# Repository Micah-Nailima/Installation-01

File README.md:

# Installation-01
A 75% keyboard with magnetic rotary encoders and a build in USB hub for additional peripherals such as a numpad and midi controller.

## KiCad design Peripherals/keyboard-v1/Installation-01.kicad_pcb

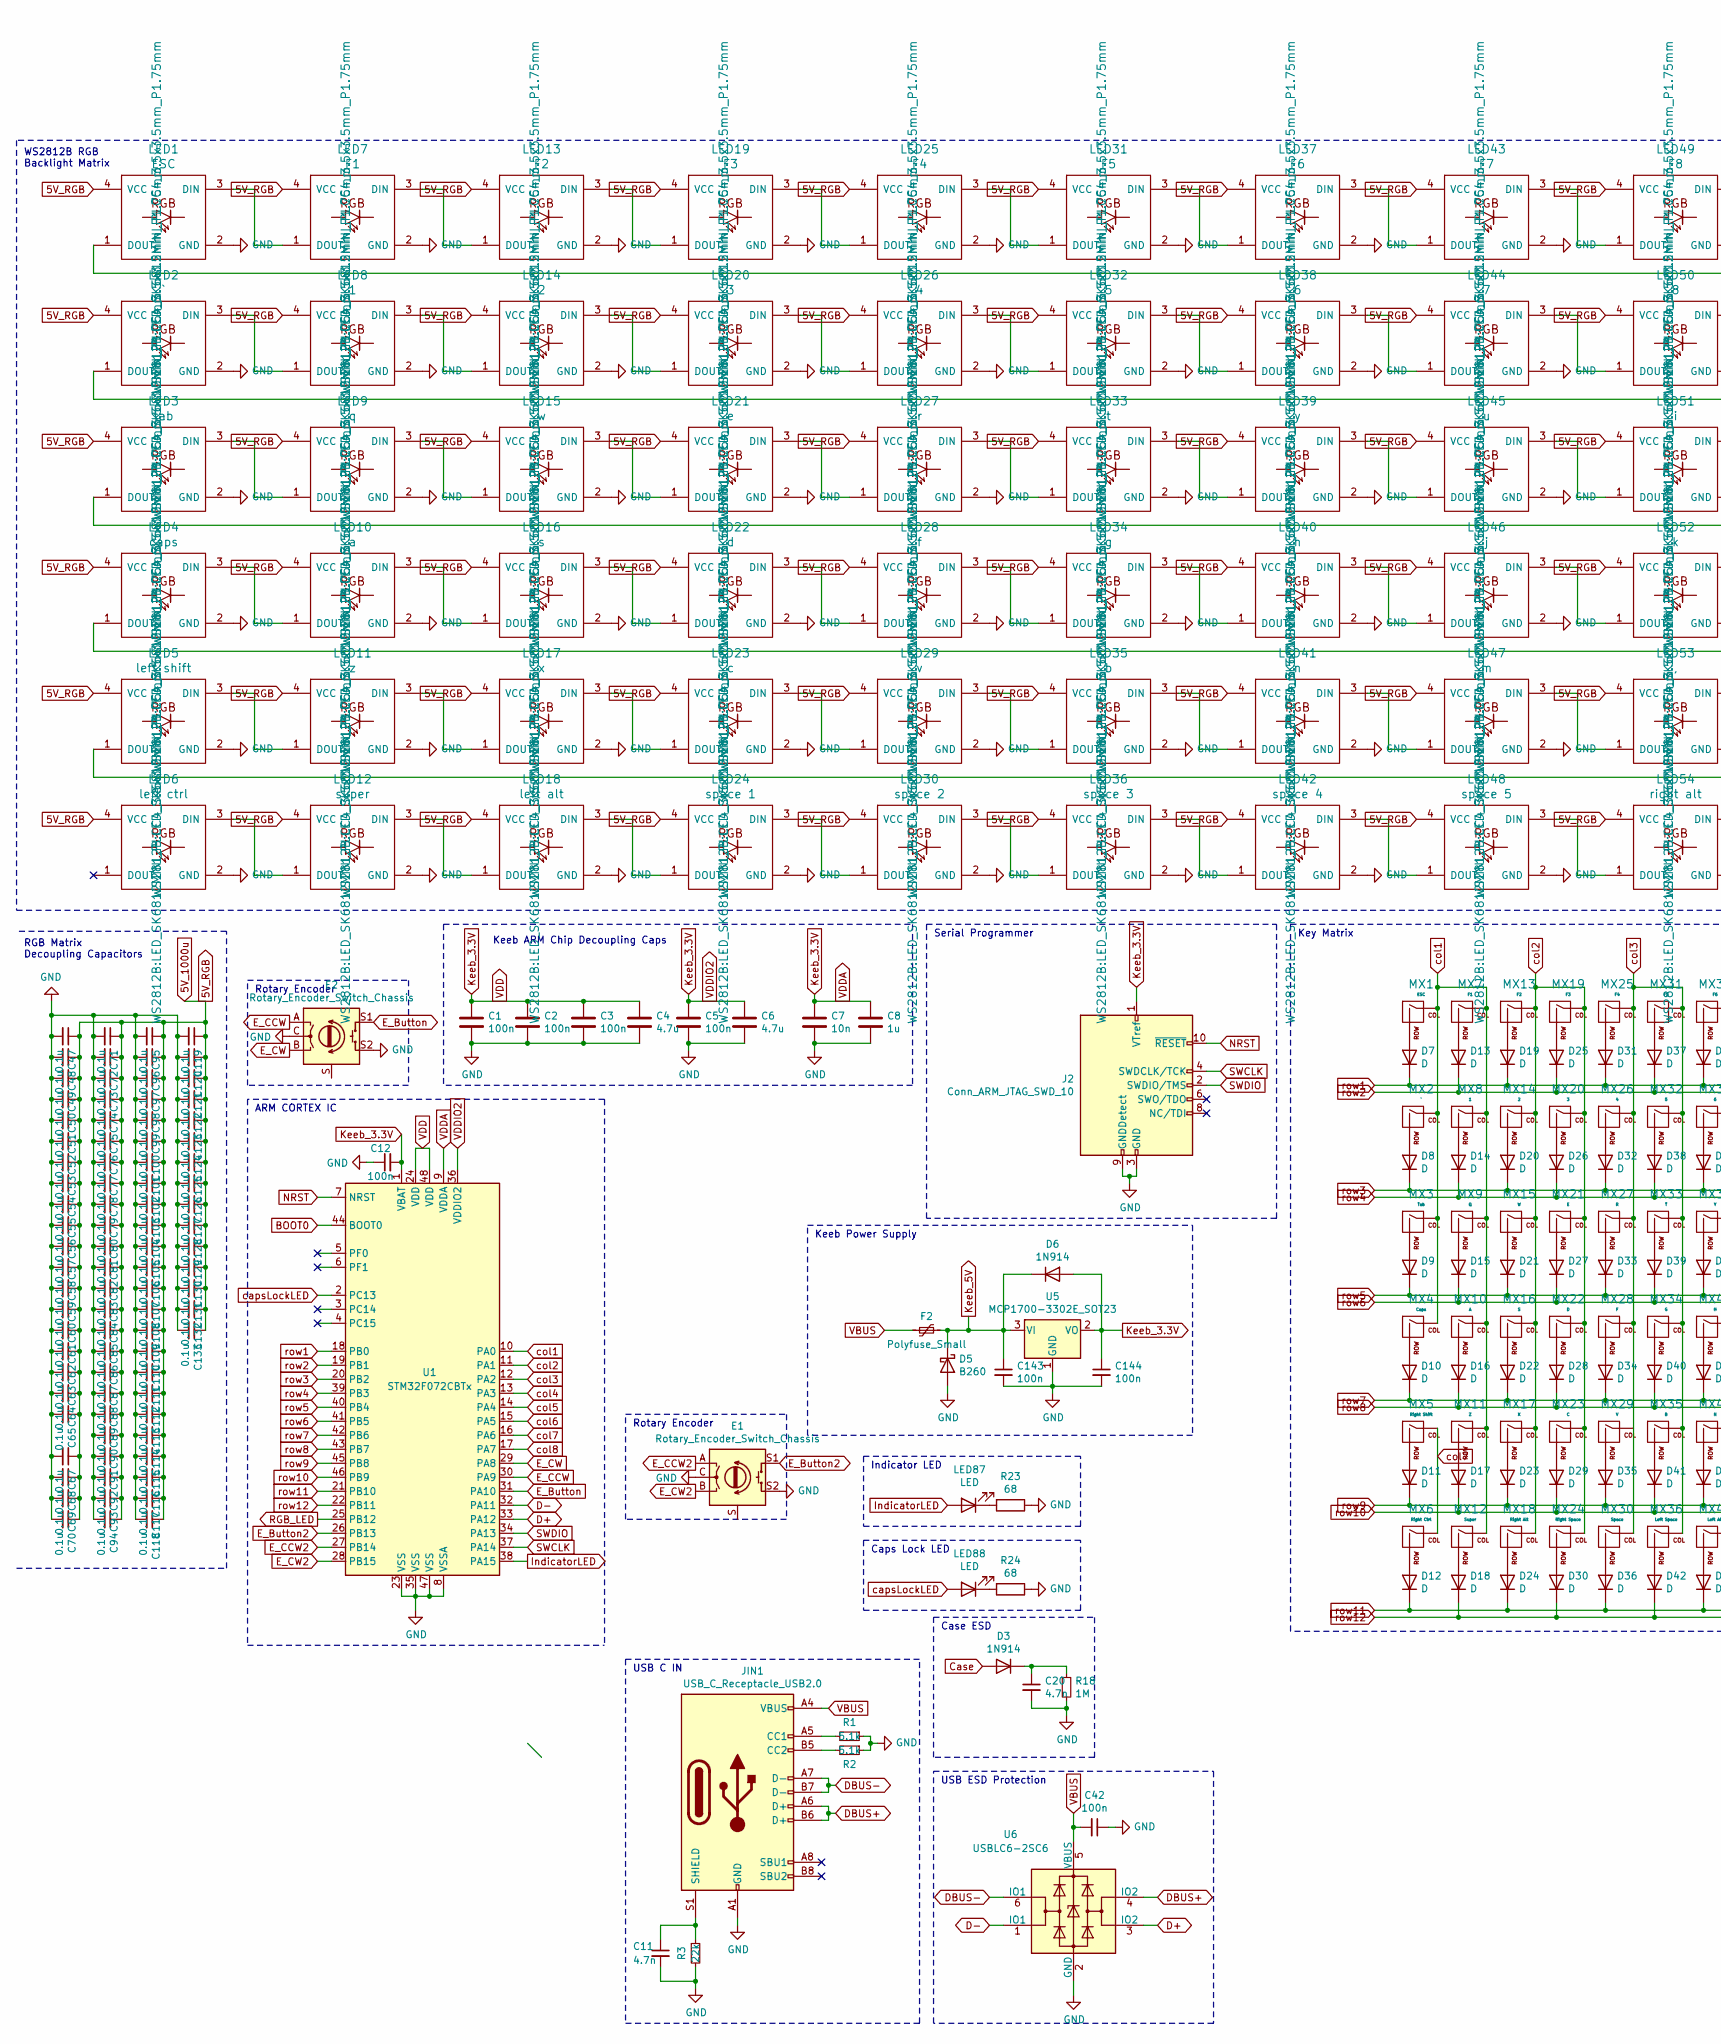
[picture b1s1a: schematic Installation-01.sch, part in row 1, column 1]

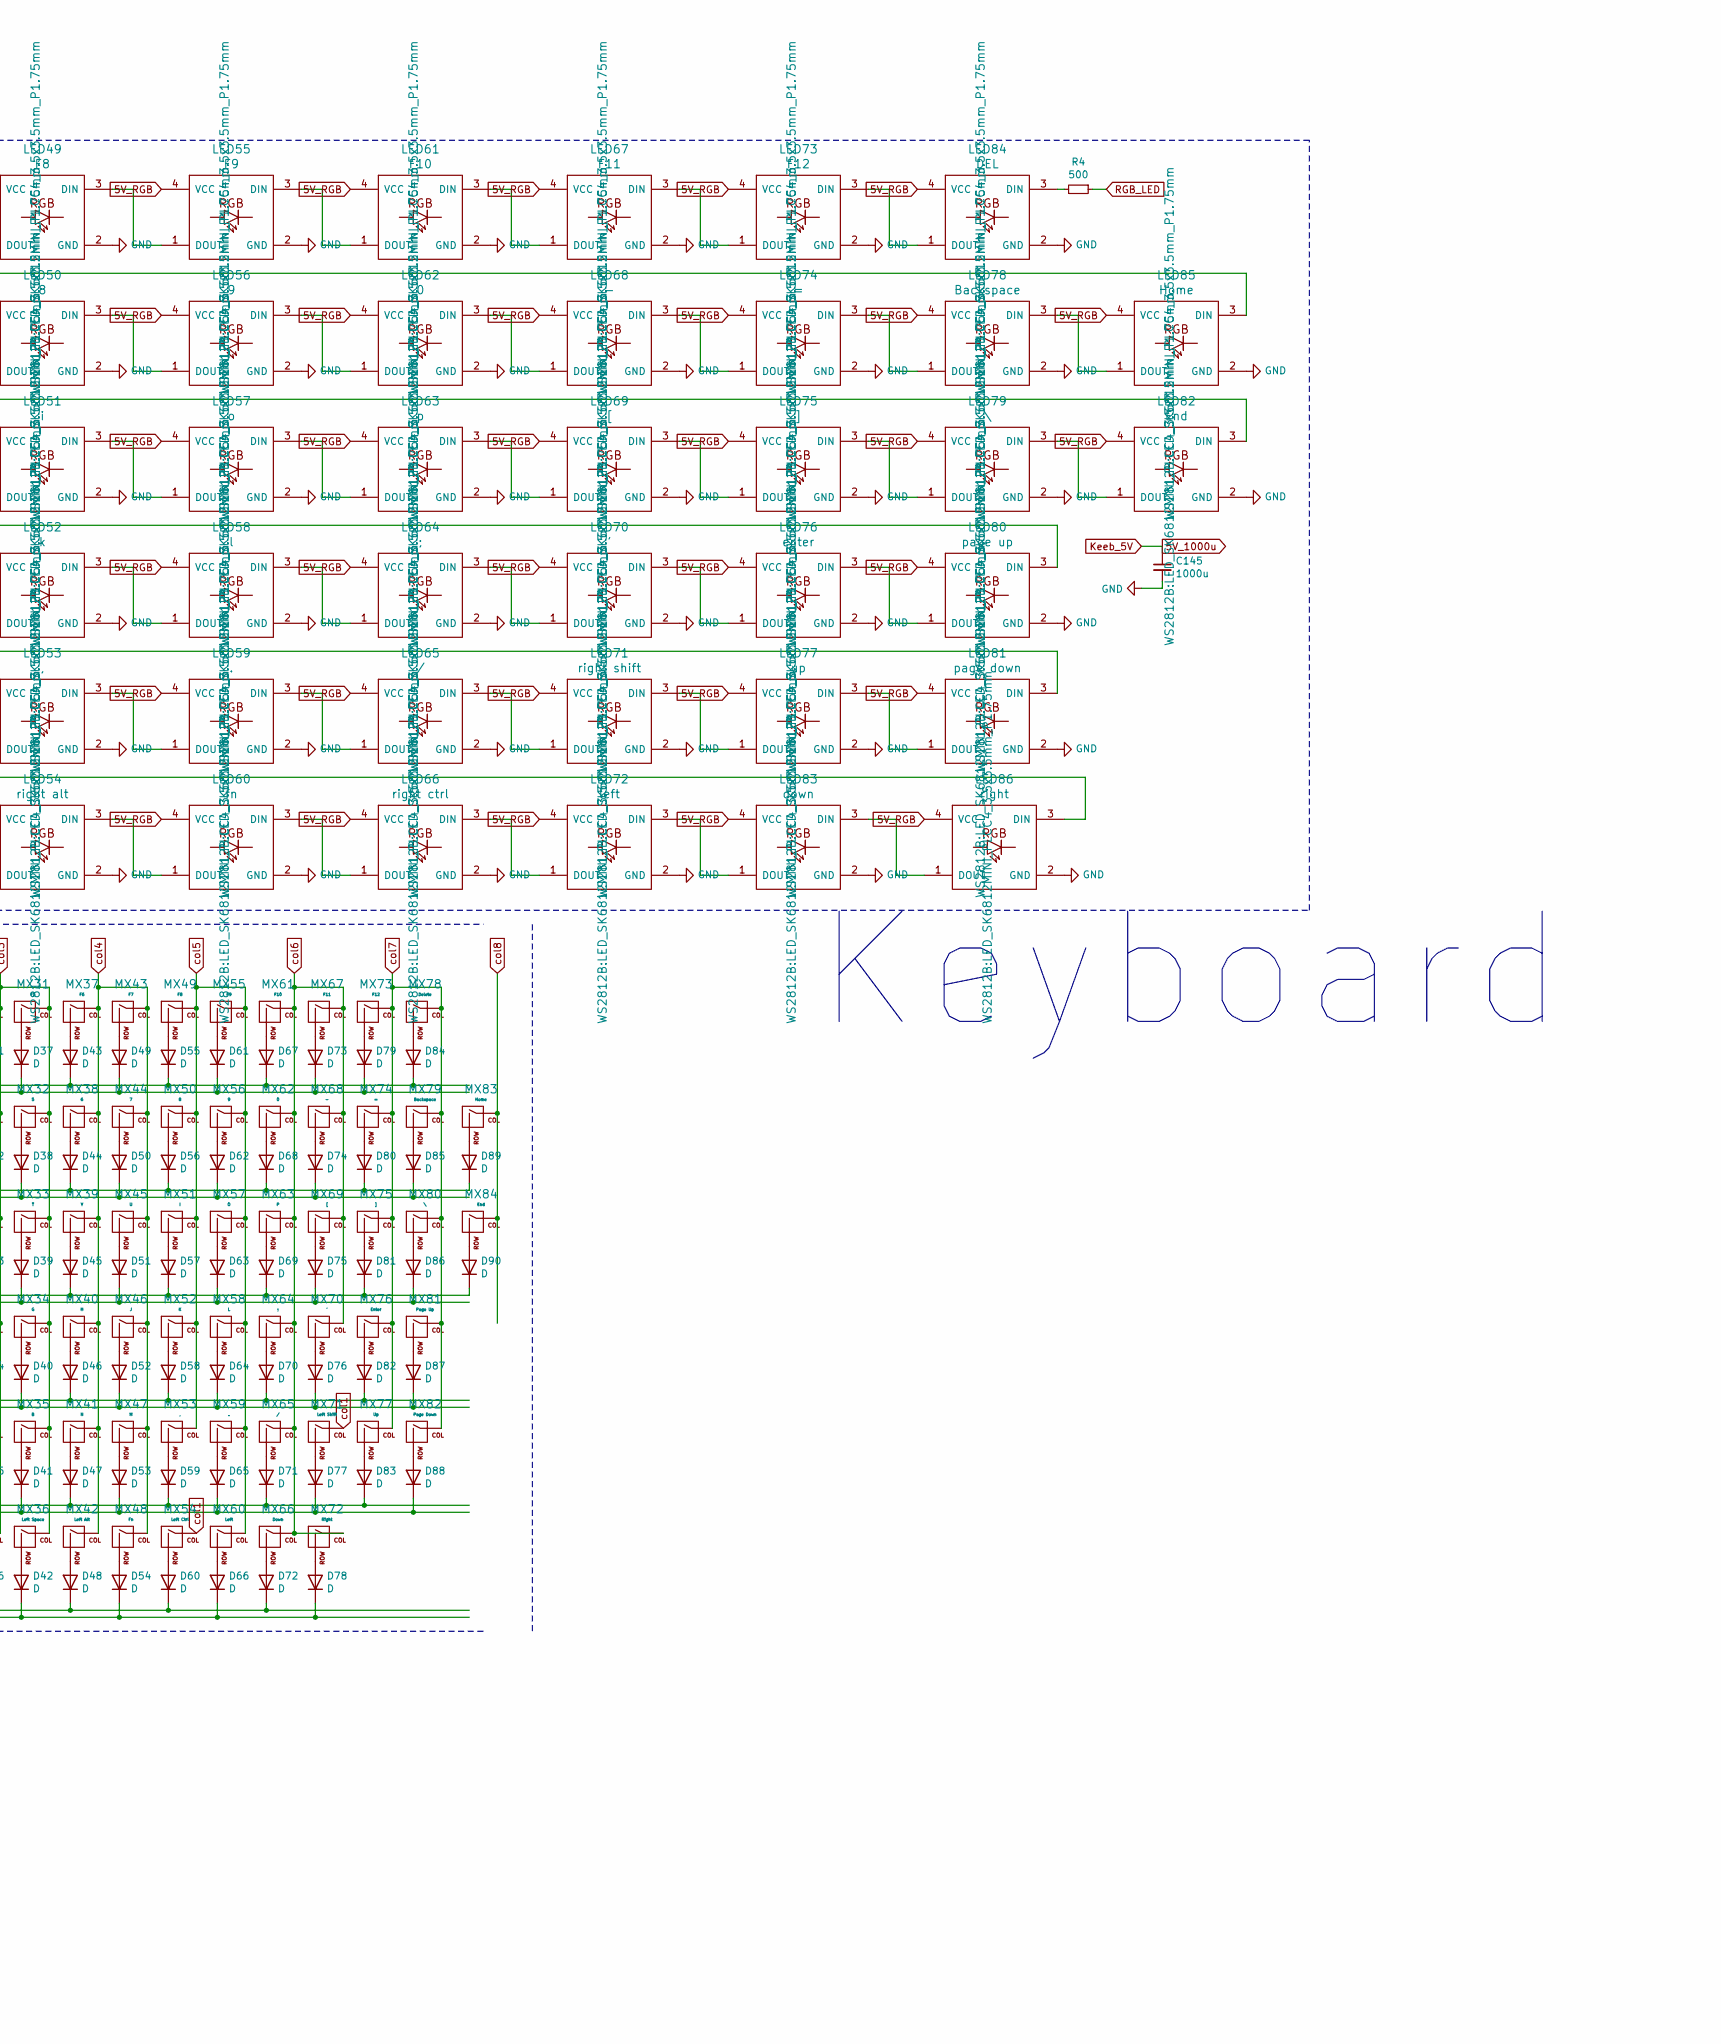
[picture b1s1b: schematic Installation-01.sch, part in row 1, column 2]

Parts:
C1, C2, C3, C5, C12, C42, C143, C144: 100n; CP_EIA-2012-15_AVX-P
C4, C6: 4.7u; CP_EIA-2012-15_AVX-P
C7: 10n; CP_EIA-2012-15_AVX-P
C8: 1u; CP_EIA-2012-15_AVX-P
C11, C20: 4.7n; CP_EIA-2012-15_AVX-P
C47, C48, C49, C50, C51, C52, C53, C54, C55, C56, C57, C58, C59, C60, C61, C62, C63, C64, C65, C67, C68, C69, C70, C71, C72, C73, C74, C75, C76, C77, C78, C79, C80, C81, C82, C83, C84, C85, C86, C87, C88, C89, C90, C91, C92, C93, C94, C95, C96, C97, C98, C99, C100, C101, C102, C103, C104, C105, C106, C107, C108, C109, C110, C111, C112, C113, C114, C115, C116, C117, C118, C119, C120, C121, C122, C123, C124, C125, C126, C127, C128, C129, C130, C131, C132, C133: 0.1u; CP_EIA-2012-15_AVX-P
C145: 1000u; CP_EIA-2012-15_AVX-P
D3, D6: 1N914; D_DO-35_SOD27_P7.62mm_Horizontal
D5: B260; D_SMB
D7, D8, D9, D10, D11, D12, D13, D14, D15, D16, D17, D18, D19, D20, D21, D22, D23, D24, D25, D26, D27, D28, D29, D30, D31, D32, D33, D34, D35, D36, D37, D38, D39, D40, D41, D42, D43, D44, D45, D46, D47, D48, D49, D50, D51, D52, D53, D54, D55, D56, D57, D58, D59, D60, D61, D62, D63, D64, D65, D66, D67, D68, D69, D70, D71, D72, D73, D74, D75, D76, D77, D78, D79, D80, D81, D82, D83, D84, D85, D86, D87, D88, D89, D90: D; D_SOD-123
E1, E2: Rotary_Encoder_Switch_Chassis; ALPS_EC11E
F2: Polyfuse_Small; Fuse_1206_3216Metric
J2: Conn_ARM_JTAG_SWD_10; PinSocket_2x05_P1.00mm_Vertical_SMD
JIN1: USB_C_Receptacle_USB2.0; USB_C_GCT_USB4085
LED1: ESC; LED_SK6812MINI_PLCC4_3.5x3.5mm_P1.75mm
LED2: `; LED_SK6812MINI_PLCC4_3.5x3.5mm_P1.75mm
LED3: tab; LED_SK6812MINI_PLCC4_3.5x3.5mm_P1.75mm
LED4: caps; LED_SK6812MINI_PLCC4_3.5x3.5mm_P1.75mm
LED5: left shift; LED_SK6812MINI_PLCC4_3.5x3.5mm_P1.75mm
LED6: left ctrl; LED_SK6812MINI_PLCC4_3.5x3.5mm_P1.75mm
LED7: F1; LED_SK6812MINI_PLCC4_3.5x3.5mm_P1.75mm
LED8: 1; LED_SK6812MINI_PLCC4_3.5x3.5mm_P1.75mm
LED9: q; LED_SK6812MINI_PLCC4_3.5x3.5mm_P1.75mm
LED10: a; LED_SK6812MINI_PLCC4_3.5x3.5mm_P1.75mm
LED11: z; LED_SK6812MINI_PLCC4_3.5x3.5mm_P1.75mm
LED12: super; LED_SK6812MINI_PLCC4_3.5x3.5mm_P1.75mm
LED13: F2; LED_SK6812MINI_PLCC4_3.5x3.5mm_P1.75mm
LED14: 2; LED_SK6812MINI_PLCC4_3.5x3.5mm_P1.75mm
LED15: w; LED_SK6812MINI_PLCC4_3.5x3.5mm_P1.75mm
LED16: s; LED_SK6812MINI_PLCC4_3.5x3.5mm_P1.75mm
LED17: x; LED_SK6812MINI_PLCC4_3.5x3.5mm_P1.75mm
LED18: left alt; LED_SK6812MINI_PLCC4_3.5x3.5mm_P1.75mm
LED19: F3; LED_SK6812MINI_PLCC4_3.5x3.5mm_P1.75mm
LED20: 3; LED_SK6812MINI_PLCC4_3.5x3.5mm_P1.75mm
LED21: e; LED_SK6812MINI_PLCC4_3.5x3.5mm_P1.75mm
LED22: d; LED_SK6812MINI_PLCC4_3.5x3.5mm_P1.75mm
LED23: c; LED_SK6812MINI_PLCC4_3.5x3.5mm_P1.75mm
LED24: space 1; LED_SK6812MINI_PLCC4_3.5x3.5mm_P1.75mm
LED25: F4; LED_SK6812MINI_PLCC4_3.5x3.5mm_P1.75mm
LED26: 4; LED_SK6812MINI_PLCC4_3.5x3.5mm_P1.75mm
LED27: r; LED_SK6812MINI_PLCC4_3.5x3.5mm_P1.75mm
LED28: f; LED_SK6812MINI_PLCC4_3.5x3.5mm_P1.75mm
LED29: v; LED_SK6812MINI_PLCC4_3.5x3.5mm_P1.75mm
LED30: space 2; LED_SK6812MINI_PLCC4_3.5x3.5mm_P1.75mm
LED31: F5; LED_SK6812MINI_PLCC4_3.5x3.5mm_P1.75mm
LED32: 5; LED_SK6812MINI_PLCC4_3.5x3.5mm_P1.75mm
LED33: t; LED_SK6812MINI_PLCC4_3.5x3.5mm_P1.75mm
LED34: g; LED_SK6812MINI_PLCC4_3.5x3.5mm_P1.75mm
LED35: b; LED_SK6812MINI_PLCC4_3.5x3.5mm_P1.75mm
LED36: space 3; LED_SK6812MINI_PLCC4_3.5x3.5mm_P1.75mm
LED37: F6; LED_SK6812MINI_PLCC4_3.5x3.5mm_P1.75mm
LED38: 6; LED_SK6812MINI_PLCC4_3.5x3.5mm_P1.75mm
LED39: y; LED_SK6812MINI_PLCC4_3.5x3.5mm_P1.75mm
LED40: h; LED_SK6812MINI_PLCC4_3.5x3.5mm_P1.75mm
LED41: n; LED_SK6812MINI_PLCC4_3.5x3.5mm_P1.75mm
LED42: space 4; LED_SK6812MINI_PLCC4_3.5x3.5mm_P1.75mm
LED43: F7; LED_SK6812MINI_PLCC4_3.5x3.5mm_P1.75mm
LED44: 7; LED_SK6812MINI_PLCC4_3.5x3.5mm_P1.75mm
LED45: u; LED_SK6812MINI_PLCC4_3.5x3.5mm_P1.75mm
LED46: j; LED_SK6812MINI_PLCC4_3.5x3.5mm_P1.75mm
LED47: m; LED_SK6812MINI_PLCC4_3.5x3.5mm_P1.75mm
LED48: space 5; LED_SK6812MINI_PLCC4_3.5x3.5mm_P1.75mm
LED49: F8; LED_SK6812MINI_PLCC4_3.5x3.5mm_P1.75mm
LED50: 8; LED_SK6812MINI_PLCC4_3.5x3.5mm_P1.75mm
LED51: i; LED_SK6812MINI_PLCC4_3.5x3.5mm_P1.75mm
LED52: k; LED_SK6812MINI_PLCC4_3.5x3.5mm_P1.75mm
LED53: ,; LED_SK6812MINI_PLCC4_3.5x3.5mm_P1.75mm
LED54: right alt; LED_SK6812MINI_PLCC4_3.5x3.5mm_P1.75mm
LED55: F9; LED_SK6812MINI_PLCC4_3.5x3.5mm_P1.75mm
LED56: 9; LED_SK6812MINI_PLCC4_3.5x3.5mm_P1.75mm
LED57: o; LED_SK6812MINI_PLCC4_3.5x3.5mm_P1.75mm
LED58: l; LED_SK6812MINI_PLCC4_3.5x3.5mm_P1.75mm
LED59: .; LED_SK6812MINI_PLCC4_3.5x3.5mm_P1.75mm
LED60: fn; LED_SK6812MINI_PLCC4_3.5x3.5mm_P1.75mm
LED61: F10; LED_SK6812MINI_PLCC4_3.5x3.5mm_P1.75mm
LED62: 0; LED_SK6812MINI_PLCC4_3.5x3.5mm_P1.75mm
LED63: p; LED_SK6812MINI_PLCC4_3.5x3.5mm_P1.75mm
LED64: ;; LED_SK6812MINI_PLCC4_3.5x3.5mm_P1.75mm
LED65: /; LED_SK6812MINI_PLCC4_3.5x3.5mm_P1.75mm
LED66: right ctrl; LED_SK6812MINI_PLCC4_3.5x3.5mm_P1.75mm
LED67: F11; LED_SK6812MINI_PLCC4_3.5x3.5mm_P1.75mm
LED68: -; LED_SK6812MINI_PLCC4_3.5x3.5mm_P1.75mm
LED69: [; LED_SK6812MINI_PLCC4_3.5x3.5mm_P1.75mm
LED70: '; LED_SK6812MINI_PLCC4_3.5x3.5mm_P1.75mm
LED71: right shift; LED_SK6812MINI_PLCC4_3.5x3.5mm_P1.75mm
LED72: left; LED_SK6812MINI_PLCC4_3.5x3.5mm_P1.75mm
LED73: F12; LED_SK6812MINI_PLCC4_3.5x3.5mm_P1.75mm
LED74: =; LED_SK6812MINI_PLCC4_3.5x3.5mm_P1.75mm
LED75: ]; LED_SK6812MINI_PLCC4_3.5x3.5mm_P1.75mm
LED76: enter; LED_SK6812MINI_PLCC4_3.5x3.5mm_P1.75mm
LED77: up; LED_SK6812MINI_PLCC4_3.5x3.5mm_P1.75mm
LED78: Backspace; LED_SK6812MINI_PLCC4_3.5x3.5mm_P1.75mm
LED79: \\; LED_SK6812MINI_PLCC4_3.5x3.5mm_P1.75mm
LED80: page up; LED_SK6812MINI_PLCC4_3.5x3.5mm_P1.75mm
LED81: page down; LED_SK6812MINI_PLCC4_3.5x3.5mm_P1.75mm
LED82: End; LED_SK6812MINI_PLCC4_3.5x3.5mm_P1.75mm
LED83: down; LED_SK6812MINI_PLCC4_3.5x3.5mm_P1.75mm
LED84: DEL; LED_SK6812MINI_PLCC4_3.5x3.5mm_P1.75mm
LED85: Home; LED_SK6812MINI_PLCC4_3.5x3.5mm_P1.75mm
LED86: right; LED_SK6812MINI_PLCC4_3.5x3.5mm_P1.75mm
LED87, LED88: LED; LED_0805_2012Metric
MX1: ESC; MXOnly-1U-Hotswap
MX2: `; MXOnly-1U-Hotswap
MX3: Tab; MXOnly-1.5U-Hotswap
MX4: Caps; MXOnly-1.75U-Hotswap
MX5: Right Shift; MXOnly-2U-Hotswap
MX6: Right Ctrl; MXOnly-1U-Hotswap
MX7: F1; MXOnly-1U-Hotswap
MX8: 1; MXOnly-1U-Hotswap
MX9: Q; MXOnly-1U-Hotswap
MX10: A; MXOnly-1U-Hotswap
MX11: Z; MXOnly-1U-Hotswap
MX12: Super; MXOnly-1.25U-Hotswap
MX13: F2; MXOnly-1U-Hotswap
MX14: 2; MXOnly-1U-Hotswap
MX15: W; MXOnly-1U-Hotswap
MX16: S; MXOnly-1U-Hotswap
MX17: X; MXOnly-1U-Hotswap
MX18: Right Alt; MXOnly-1U-Hotswap
MX19: F3; MXOnly-1U-Hotswap
MX20: 3; MXOnly-1U-Hotswap
MX21: E; MXOnly-1U-Hotswap
MX22: D; MXOnly-1U-Hotswap
MX23: C; MXOnly-1U-Hotswap
MX24: Right Space; MXOnly-2.75U-Hotswap
MX25: F4; MXOnly-1U-Hotswap
MX26: 4; MXOnly-1U-Hotswap
MX27: R; MXOnly-1U-Hotswap
MX28: F; MXOnly-1U-Hotswap
MX29: V; MXOnly-1U-Hotswap
MX30: Space; MXOnly-6.25U-Hotswap
MX31: F5; MXOnly-1U-Hotswap
MX32: 5; MXOnly-1U-Hotswap
MX33: T; MXOnly-1U-Hotswap
MX34: G; MXOnly-1U-Hotswap
MX35: B; MXOnly-1U-Hotswap
MX36: Left Space; MXOnly-2.75U-Hotswap
MX37: F6; MXOnly-1U-Hotswap
MX38: 6; MXOnly-1U-Hotswap
MX39: Y; MXOnly-1U-Hotswap
MX40: H; MXOnly-1U-Hotswap
MX41: N; MXOnly-1U-Hotswap
MX42: Left Alt; MXOnly-1.25U-Hotswap
MX43: F7; MXOnly-1U-Hotswap
MX44: 7; MXOnly-1U-Hotswap
MX45: U; MXOnly-1U-Hotswap
MX46: J; MXOnly-1U-Hotswap
MX47: M; MXOnly-1U-Hotswap
MX48: Fn; MXOnly-1U-Hotswap
MX49: F8; MXOnly-1U-Hotswap
MX50: 8; MXOnly-1U-Hotswap
MX51: I; MXOnly-1U-Hotswap
MX52: K; MXOnly-1U-Hotswap
MX53: ,; MXOnly-1U-Hotswap
MX54: Left Ctrl; MXOnly-1.25U-Hotswap
MX55: F9; MXOnly-1U-Hotswap
MX56: 9; MXOnly-1U-Hotswap
MX57: O; MXOnly-1U-Hotswap
MX58: L; MXOnly-1U-Hotswap
MX59: .; MXOnly-1U-Hotswap
MX60: Left; MXOnly-1U-Hotswap
MX61: F10; MXOnly-1U-Hotswap
MX62: 0; MXOnly-1U-Hotswap
MX63: P; MXOnly-1U-Hotswap
MX64: ;; MXOnly-1U-Hotswap
MX65: /; MXOnly-1U-Hotswap
MX66: Down; MXOnly-1U-Hotswap
MX67: F11; MXOnly-1U-Hotswap
MX68: -; MXOnly-1U-Hotswap
MX69: [; MXOnly-1U-Hotswap
MX70: '; MXOnly-1U-Hotswap
MX71: Left Shift; MXOnly-2.25U-Hotswap
MX72: Right; MXOnly-1U-Hotswap
MX73: F12; MXOnly-1U-Hotswap
MX74: =; MXOnly-1U-Hotswap
MX75: ]; MXOnly-1U-Hotswap
MX76: Enter; MXOnly-2.25U-Hotswap
MX77: Up; MXOnly-1U-Hotswap
MX78: Delete; MXOnly-1U-Hotswap
MX79: Backspace; MXOnly-2U-Hotswap
MX80: \\; MXOnly-1.5U-Hotswap
MX81: Page Up; MXOnly-1U-Hotswap
MX82: Page Down; MXOnly-1U-Hotswap
MX83: Home; MXOnly-1U-Hotswap
MX84: End; MXOnly-1U-Hotswap
R1, R2: 5.1k; R_0805_2012Metric
R3: 22k; R_0805_2012Metric
R4: 500; R_0805_2012Metric
R18: 1M; R_0805_2012Metric
R23, R24: 68; R_0805_2012Metric
U1: STM32F072CBTx; LQFP-48_7x7mm_P0.5mm
U5: MCP1700-3302E_SOT23; SOT-23
U6: USBLC6-2SC6; SOT-23-6

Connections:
5V_1000u: C47.1, C48.1, C49.1, C50.1, C51.1, C52.1, C53.1, C54.1, C55.1, C56.1, C57.1, C58.1, C59.1, C60.1, C61.1, C62.1, C63.1, C64.1, C65.1, C67.1, C68.1, C69.1, C70.1, C71.1, C72.1, C73.1, C74.1, C75.1, C76.1, C77.1, C78.1, C79.1, C80.1, C81.1, C82.1, C83.1, C84.1, C85.1, C86.1, C87.1, C88.1, C89.1, C90.1, C91.1, C92.1, C93.1, C94.1, C95.1, C96.1, C97.1, C98.1, C99.1, C100.1, C101.1, C102.1, C103.1, C104.1, C105.1, C106.1, C107.1, C108.1, C109.1, C110.1, C111.1, C112.1, C113.1, C114.1, C115.1, C116.1, C117.1, C118.1, C119.1, C120.1, C121.1, C122.1, C123.1, C124.1, C125.1, C126.1, C127.1, C128.1, C129.1, C130.1, C131.1, C132.1, C133.1, C143.1, C145.1, D5.1 (K), D6.1 (K), F2.1, LED1.4 (VCC), LED2.4 (VCC), LED3.4 (VCC), LED4.4 (VCC), LED5.4 (VCC), LED6.4 (VCC), LED7.4 (VCC), LED8.4 (VCC), LED9.4 (VCC), LED10.4 (VCC), LED11.4 (VCC), LED12.4 (VCC), LED13.4 (VCC), LED14.4 (VCC), LED15.4 (VCC), LED16.4 (VCC), LED17.4 (VCC), LED18.4 (VCC), LED19.4 (VCC), LED20.4 (VCC), LED21.4 (VCC), LED22.4 (VCC), LED23.4 (VCC), LED24.4 (VCC), LED25.4 (VCC), LED26.4 (VCC), LED27.4 (VCC), LED28.4 (VCC), LED29.4 (VCC), LED30.4 (VCC), LED31.4 (VCC), LED32.4 (VCC), LED33.4 (VCC), LED34.4 (VCC), LED35.4 (VCC), LED36.4 (VCC), LED37.4 (VCC), LED38.4 (VCC), LED39.4 (VCC), LED40.4 (VCC), LED41.4 (VCC), LED42.4 (VCC), LED43.4 (VCC), LED44.4 (VCC), LED45.4 (VCC), LED46.4 (VCC), LED47.4 (VCC), LED48.4 (VCC), LED49.4 (VCC), LED50.4 (VCC), LED51.4 (VCC), LED52.4 (VCC), LED53.4 (VCC), LED54.4 (VCC), LED55.4 (VCC), LED56.4 (VCC), LED57.4 (VCC), LED58.4 (VCC), LED59.4 (VCC), LED60.4 (VCC), LED61.4 (VCC), LED62.4 (VCC), LED63.4 (VCC), LED64.4 (VCC), LED65.4 (VCC), LED66.4 (VCC), LED67.4 (VCC), LED68.4 (VCC), LED69.4 (VCC), LED70.4 (VCC), LED71.4 (VCC), LED72.4 (VCC), LED73.4 (VCC), LED74.4 (VCC), LED75.4 (VCC), LED76.4 (VCC), LED77.4 (VCC), LED78.4 (VCC), LED79.4 (VCC), LED80.4 (VCC), LED81.4 (VCC), LED82.4 (VCC), LED83.4 (VCC), LED84.4 (VCC), LED85.4 (VCC), LED86.4 (VCC), U5.3 (VI)
BOOT0: U1.44 (BOOT0)
Case: D3.2 (A)
D+: U1.33 (PA12), U6.3 (IO2)
D-: U1.32 (PA11), U6.1 (IO1)
DBUS+: JIN1.A6 (D+), JIN1.B6 (D+), U6.4 (IO2)
DBUS-: JIN1.A7 (D-), JIN1.B7 (D-), U6.6 (IO1)
E_Button: E2.S1, U1.31 (PA10)
E_Button2: E1.S1, U1.26 (PB13)
E_CCW: E2.A, U1.30 (PA9)
E_CCW2: E1.A, U1.27 (PB14)
E_CW: E2.B, U1.29 (PA8)
E_CW2: E1.B, U1.28 (PB15)
GND: C1.2, C2.2, C3.2, C4.2, C5.2, C6.2, C7.2, C8.2, C11.2, C12.1, C20.2, C42.1, C47.2, C48.2, C49.2, C50.2, C51.2, C52.2, C53.2, C54.2, C55.2, C56.2, C57.2, C58.2, C59.2, C60.2, C61.2, C62.2, C63.2, C64.2, C65.2, C67.2, C68.2, C69.2, C70.2, C71.2, C72.2, C73.2, C74.2, C75.2, C76.2, C77.2, C78.2, C79.2, C80.2, C81.2, C82.2, C83.2, C84.2, C85.2, C86.2, C87.2, C88.2, C89.2, C90.2, C91.2, C92.2, C93.2, C94.2, C95.2, C96.2, C97.2, C98.2, C99.2, C100.2, C101.2, C102.2, C103.2, C104.2, C105.2, C106.2, C107.2, C108.2, C109.2, C110.2, C111.2, C112.2, C113.2, C114.2, C115.2, C116.2, C117.2, C118.2, C119.2, C120.2, C121.2, C122.2, C123.2, C124.2, C125.2, C126.2, C127.2, C128.2, C129.2, C130.2, C131.2, C132.2, C133.2, C143.2, C144.2, C145.2, D5.2 (A), E1.C, E1.S2, E2.C, E2.S2, J2.3 (GND), J2.5 (GND), J2.9 (GNDDetect), JIN1.A1 (GND), JIN1.A12 (GND), JIN1.B1 (GND), JIN1.B12 (GND), LED1.2 (GND), LED2.2 (GND), LED3.2 (GND), LED4.2 (GND), LED5.2 (GND), LED6.2 (GND), LED7.2 (GND), LED8.2 (GND), LED9.2 (GND), LED10.2 (GND), LED11.2 (GND), LED12.2 (GND), LED13.2 (GND), LED14.2 (GND), LED15.2 (GND), LED16.2 (GND), LED17.2 (GND), LED18.2 (GND), LED19.2 (GND), LED20.2 (GND), LED21.2 (GND), LED22.2 (GND), LED23.2 (GND), LED24.2 (GND), LED25.2 (GND), LED26.2 (GND), LED27.2 (GND), LED28.2 (GND), LED29.2 (GND), LED30.2 (GND), LED31.2 (GND), LED32.2 (GND), LED33.2 (GND), LED34.2 (GND), LED35.2 (GND), LED36.2 (GND), LED37.2 (GND), LED38.2 (GND), LED39.2 (GND), LED40.2 (GND), LED41.2 (GND), LED42.2 (GND), LED43.2 (GND), LED44.2 (GND), LED45.2 (GND), LED46.2 (GND), LED47.2 (GND), LED48.2 (GND), LED49.2 (GND), LED50.2 (GND), LED51.2 (GND), LED52.2 (GND), LED53.2 (GND), LED54.2 (GND), LED55.2 (GND), LED56.2 (GND), LED57.2 (GND), LED58.2 (GND), LED59.2 (GND), LED60.2 (GND), LED61.2 (GND), LED62.2 (GND), LED63.2 (GND), LED64.2 (GND), LED65.2 (GND), LED66.2 (GND), LED67.2 (GND), LED68.2 (GND), LED69.2 (GND), LED70.2 (GND), LED71.2 (GND), LED72.2 (GND), LED73.2 (GND), LED74.2 (GND), LED75.2 (GND), LED76.2 (GND), LED77.2 (GND), LED78.2 (GND), LED79.2 (GND), LED80.2 (GND), LED81.2 (GND), LED82.2 (GND), LED83.2 (GND), LED84.2 (GND), LED85.2 (GND), LED86.2 (GND), R1.1, R2.1, R3.2, R18.2, R23.1, R24.1, U1.8 (VSSA), U1.23 (VSS), U1.35 (VSS), U1.47 (VSS), U5.1 (GND), U6.2 (GND)
IndicatorLED: LED87.2 (A), U1.38 (PA15)
Keeb_3.3V: C1.1, C2.1, C3.1, C4.1, C5.1, C6.1, C7.1, C8.1, C12.2, C144.1, D6.2 (A), J2.1 (VTref), U1.1 (VBAT), U1.9 (VDDA), U1.24 (VDD), U1.36 (VDDIO2), U1.48 (VDD), U5.2 (VO)
NRST: J2.10 (~RESET~), U1.7 (NRST)
unnamed: C11.1, JIN1.S1 (SHIELD), R3.1
unnamed: C20.1, D3.1 (K), R18.1
unnamed: D7.2 (A), MX1.2 (ROW)
unnamed: D8.2 (A), MX2.2 (ROW)
unnamed: D9.2 (A), MX3.2 (ROW)
unnamed: D10.2 (A), MX4.2 (ROW)
unnamed: D11.2 (A), MX5.2 (ROW)
unnamed: D12.2 (A), MX6.2 (ROW)
unnamed: D13.2 (A), MX7.2 (ROW)
unnamed: D14.2 (A), MX8.2 (ROW)
unnamed: D15.2 (A), MX9.2 (ROW)
unnamed: D16.2 (A), MX10.2 (ROW)
unnamed: D17.2 (A), MX11.2 (ROW)
unnamed: D18.2 (A), MX12.2 (ROW)
unnamed: D19.2 (A), MX13.2 (ROW)
unnamed: D20.2 (A), MX14.2 (ROW)
unnamed: D21.2 (A), MX15.2 (ROW)
unnamed: D22.2 (A), MX16.2 (ROW)
unnamed: D23.2 (A), MX17.2 (ROW)
unnamed: D24.2 (A), MX18.2 (ROW)
unnamed: D25.2 (A), MX19.2 (ROW)
unnamed: D26.2 (A), MX20.2 (ROW)
unnamed: D27.2 (A), MX21.2 (ROW)
unnamed: D28.2 (A), MX22.2 (ROW)
unnamed: D29.2 (A), MX23.2 (ROW)
unnamed: D30.2 (A), MX24.2 (ROW)
unnamed: D31.2 (A), MX25.2 (ROW)
unnamed: D32.2 (A), MX26.2 (ROW)
unnamed: D33.2 (A), MX27.2 (ROW)
unnamed: D34.2 (A), MX28.2 (ROW)
unnamed: D35.2 (A), MX29.2 (ROW)
unnamed: D36.2 (A), MX30.2 (ROW)
unnamed: D37.2 (A), MX31.2 (ROW)
unnamed: D38.2 (A), MX32.2 (ROW)
unnamed: D39.2 (A), MX33.2 (ROW)
unnamed: D40.2 (A), MX34.2 (ROW)
unnamed: D41.2 (A), MX35.2 (ROW)
unnamed: D42.2 (A), MX36.2 (ROW)
unnamed: D43.2 (A), MX37.2 (ROW)
unnamed: D44.2 (A), MX38.2 (ROW)
unnamed: D45.2 (A), MX39.2 (ROW)
unnamed: D46.2 (A), MX40.2 (ROW)
unnamed: D47.2 (A), MX41.2 (ROW)
unnamed: D48.2 (A), MX42.2 (ROW)
unnamed: D49.2 (A), MX43.2 (ROW)
unnamed: D50.2 (A), MX44.2 (ROW)
unnamed: D51.2 (A), MX45.2 (ROW)
unnamed: D52.2 (A), MX46.2 (ROW)
unnamed: D53.2 (A), MX47.2 (ROW)
unnamed: D54.2 (A), MX48.2 (ROW)
unnamed: D55.2 (A), MX49.2 (ROW)
unnamed: D56.2 (A), MX50.2 (ROW)
unnamed: D57.2 (A), MX51.2 (ROW)
unnamed: D58.2 (A), MX52.2 (ROW)
unnamed: D59.2 (A), MX53.2 (ROW)
unnamed: D60.2 (A), MX54.2 (ROW)
unnamed: D61.2 (A), MX55.2 (ROW)
unnamed: D62.2 (A), MX56.2 (ROW)
unnamed: D63.2 (A), MX57.2 (ROW)
unnamed: D64.2 (A), MX58.2 (ROW)
unnamed: D65.2 (A), MX59.2 (ROW)
unnamed: D66.2 (A), MX60.2 (ROW)
unnamed: D67.2 (A), MX61.2 (ROW)
unnamed: D68.2 (A), MX62.2 (ROW)
unnamed: D69.2 (A), MX63.2 (ROW)
unnamed: D70.2 (A), MX64.2 (ROW)
unnamed: D71.2 (A), MX65.2 (ROW)
unnamed: D72.2 (A), MX66.2 (ROW)
unnamed: D73.2 (A), MX67.2 (ROW)
unnamed: D74.2 (A), MX68.2 (ROW)
unnamed: D75.2 (A), MX69.2 (ROW)
unnamed: D76.2 (A), MX70.2 (ROW)
unnamed: D77.2 (A), MX71.2 (ROW)
unnamed: D78.2 (A), MX72.2 (ROW)
unnamed: D79.2 (A), MX73.2 (ROW)
unnamed: D80.2 (A), MX74.2 (ROW)
unnamed: D81.2 (A), MX75.2 (ROW)
unnamed: D82.2 (A), MX76.2 (ROW)
unnamed: D83.2 (A), MX77.2 (ROW)
unnamed: D84.2 (A), MX78.2 (ROW)
unnamed: D85.2 (A), MX79.2 (ROW)
unnamed: D86.2 (A), MX80.2 (ROW)
unnamed: D87.2 (A), MX81.2 (ROW)
unnamed: D88.2 (A), MX82.2 (ROW)
unnamed: D89.2 (A), MX83.2 (ROW)
unnamed: D90.2 (A), MX84.2 (ROW)
unnamed: JIN1.A5 (CC1), R1.2
unnamed: JIN1.B5 (CC2), R2.2
unnamed: LED1.1 (DOUT), LED85.3 (DIN)
unnamed: LED1.3 (DIN), LED7.1 (DOUT)
unnamed: LED2.1 (DOUT), LED82.3 (DIN)
unnamed: LED2.3 (DIN), LED8.1 (DOUT)
unnamed: LED3.1 (DOUT), LED80.3 (DIN)
unnamed: LED3.3 (DIN), LED9.1 (DOUT)
unnamed: LED4.1 (DOUT), LED81.3 (DIN)
unnamed: LED5.1 (DOUT), LED86.3 (DIN)
unnamed: LED4.3 (DIN), LED10.1 (DOUT)
unnamed: LED10.3 (DIN), LED16.1 (DOUT)
unnamed: LED5.3 (DIN), LED11.1 (DOUT)
unnamed: LED11.3 (DIN), LED17.1 (DOUT)
unnamed: LED6.3 (DIN), LED12.1 (DOUT)
unnamed: LED12.3 (DIN), LED18.1 (DOUT)
unnamed: LED7.3 (DIN), LED13.1 (DOUT)
unnamed: LED13.3 (DIN), LED19.1 (DOUT)
unnamed: LED8.3 (DIN), LED14.1 (DOUT)
unnamed: LED14.3 (DIN), LED20.1 (DOUT)
unnamed: LED9.3 (DIN), LED15.1 (DOUT)
unnamed: LED15.3 (DIN), LED21.1 (DOUT)
unnamed: LED16.3 (DIN), LED22.1 (DOUT)
unnamed: LED17.3 (DIN), LED23.1 (DOUT)
unnamed: LED18.3 (DIN), LED24.1 (DOUT)
unnamed: LED19.3 (DIN), LED25.1 (DOUT)
unnamed: LED20.3 (DIN), LED26.1 (DOUT)
unnamed: LED21.3 (DIN), LED27.1 (DOUT)
unnamed: LED22.3 (DIN), LED28.1 (DOUT)
unnamed: LED23.3 (DIN), LED29.1 (DOUT)
unnamed: LED24.3 (DIN), LED30.1 (DOUT)
unnamed: LED25.3 (DIN), LED31.1 (DOUT)
unnamed: LED26.3 (DIN), LED32.1 (DOUT)
unnamed: LED27.3 (DIN), LED33.1 (DOUT)
unnamed: LED28.3 (DIN), LED34.1 (DOUT)
unnamed: LED29.3 (DIN), LED35.1 (DOUT)
unnamed: LED30.3 (DIN), LED36.1 (DOUT)
unnamed: LED31.3 (DIN), LED37.1 (DOUT)
unnamed: LED32.3 (DIN), LED38.1 (DOUT)
unnamed: LED33.3 (DIN), LED39.1 (DOUT)
unnamed: LED34.3 (DIN), LED40.1 (DOUT)
unnamed: LED35.3 (DIN), LED41.1 (DOUT)
unnamed: LED36.3 (DIN), LED42.1 (DOUT)
unnamed: LED37.3 (DIN), LED43.1 (DOUT)
unnamed: LED38.3 (DIN), LED44.1 (DOUT)
unnamed: LED39.3 (DIN), LED45.1 (DOUT)
unnamed: LED40.3 (DIN), LED46.1 (DOUT)
unnamed: LED41.3 (DIN), LED47.1 (DOUT)
unnamed: LED42.3 (DIN), LED48.1 (DOUT)
unnamed: LED43.3 (DIN), LED49.1 (DOUT)
unnamed: LED44.3 (DIN), LED50.1 (DOUT)
unnamed: LED45.3 (DIN), LED51.1 (DOUT)
unnamed: LED46.3 (DIN), LED52.1 (DOUT)
unnamed: LED47.3 (DIN), LED53.1 (DOUT)
unnamed: LED48.3 (DIN), LED54.1 (DOUT)
unnamed: LED49.3 (DIN), LED55.1 (DOUT)
unnamed: LED50.3 (DIN), LED56.1 (DOUT)
unnamed: LED51.3 (DIN), LED57.1 (DOUT)
unnamed: LED52.3 (DIN), LED58.1 (DOUT)
unnamed: LED53.3 (DIN), LED59.1 (DOUT)
unnamed: LED54.3 (DIN), LED60.1 (DOUT)
unnamed: LED55.3 (DIN), LED61.1 (DOUT)
unnamed: LED56.3 (DIN), LED62.1 (DOUT)
unnamed: LED57.3 (DIN), LED63.1 (DOUT)
unnamed: LED58.3 (DIN), LED64.1 (DOUT)
unnamed: LED59.3 (DIN), LED65.1 (DOUT)
unnamed: LED60.3 (DIN), LED66.1 (DOUT)
unnamed: LED61.3 (DIN), LED67.1 (DOUT)
unnamed: LED62.3 (DIN), LED68.1 (DOUT)
unnamed: LED63.3 (DIN), LED69.1 (DOUT)
unnamed: LED64.3 (DIN), LED70.1 (DOUT)
unnamed: LED65.3 (DIN), LED71.1 (DOUT)
unnamed: LED66.3 (DIN), LED72.1 (DOUT)
unnamed: LED67.3 (DIN), LED73.1 (DOUT)
unnamed: LED68.3 (DIN), LED74.1 (DOUT)
unnamed: LED69.3 (DIN), LED75.1 (DOUT)
unnamed: LED70.3 (DIN), LED76.1 (DOUT)
unnamed: LED71.3 (DIN), LED77.1 (DOUT)
unnamed: LED72.3 (DIN), LED83.1 (DOUT)
unnamed: LED73.3 (DIN), LED84.1 (DOUT)
unnamed: LED74.3 (DIN), LED78.1 (DOUT)
unnamed: LED75.3 (DIN), LED79.1 (DOUT)
unnamed: LED76.3 (DIN), LED80.1 (DOUT)
unnamed: LED77.3 (DIN), LED81.1 (DOUT)
unnamed: LED78.3 (DIN), LED85.1 (DOUT)
unnamed: LED79.3 (DIN), LED82.1 (DOUT)
unnamed: LED83.3 (DIN), LED86.1 (DOUT)
unnamed: LED84.3 (DIN), R4.2
unnamed: LED87.1 (K), R23.2
unnamed: LED88.1 (K), R24.2
RGB_LED: R4.1, U1.25 (PB12)
SWCLK: J2.4 (SWDCLK/TCK), U1.37 (PA14)
SWDIO: J2.2 (SWDIO/TMS), U1.34 (PA13)
VBUS: C42.2, F2.2, JIN1.A4 (VBUS), JIN1.A9 (VBUS), JIN1.B4 (VBUS), JIN1.B9 (VBUS), U6.5 (VBUS)
capsLockLED: LED88.2 (A), U1.2 (PC13)
col1: MX1.1 (COL), MX2.1 (COL), MX3.1 (COL), MX4.1 (COL), MX7.1 (COL), MX8.1 (COL), MX9.1 (COL), MX10.1 (COL), MX11.1 (COL), MX12.1 (COL), MX54.1 (COL), MX71.1 (COL), U1.10 (PA0)
col2: MX13.1 (COL), MX14.1 (COL), MX15.1 (COL), MX16.1 (COL), MX17.1 (COL), MX18.1 (COL), MX19.1 (COL), MX20.1 (COL), MX21.1 (COL), MX22.1 (COL), MX23.1 (COL), MX24.1 (COL), U1.11 (PA1)
col3: MX25.1 (COL), MX26.1 (COL), MX27.1 (COL), MX28.1 (COL), MX29.1 (COL), MX30.1 (COL), MX31.1 (COL), MX32.1 (COL), MX33.1 (COL), MX34.1 (COL), MX35.1 (COL), MX36.1 (COL), U1.12 (PA2)
col4: MX37.1 (COL), MX38.1 (COL), MX39.1 (COL), MX40.1 (COL), MX41.1 (COL), MX42.1 (COL), MX43.1 (COL), MX44.1 (COL), MX45.1 (COL), MX46.1 (COL), MX47.1 (COL), MX48.1 (COL), U1.13 (PA3)
col5: MX49.1 (COL), MX50.1 (COL), MX51.1 (COL), MX52.1 (COL), MX53.1 (COL), MX55.1 (COL), MX56.1 (COL), MX57.1 (COL), MX58.1 (COL), MX59.1 (COL), MX60.1 (COL), U1.14 (PA4)
col6: MX61.1 (COL), MX62.1 (COL), MX63.1 (COL), MX64.1 (COL), MX65.1 (COL), MX66.1 (COL), MX67.1 (COL), MX68.1 (COL), MX69.1 (COL), MX70.1 (COL), MX72.1 (COL), U1.15 (PA5)
col7: MX5.1 (COL), MX6.1 (COL), MX73.1 (COL), MX74.1 (COL), MX75.1 (COL), MX76.1 (COL), MX77.1 (COL), MX78.1 (COL), MX79.1 (COL), MX80.1 (COL), MX81.1 (COL), MX82.1 (COL), U1.16 (PA6)
col8: MX83.1 (COL), MX84.1 (COL), U1.17 (PA7)
row1: D7.1 (K), D19.1 (K), D31.1 (K), D43.1 (K), D55.1 (K), D67.1 (K), D84.1 (K), U1.18 (PB0)
row2: D13.1 (K), D25.1 (K), D37.1 (K), D49.1 (K), D61.1 (K), D73.1 (K), D79.1 (K), U1.19 (PB1)
row3: D8.1 (K), D20.1 (K), D32.1 (K), D44.1 (K), D56.1 (K), D68.1 (K), D80.1 (K), D89.1 (K), U1.20 (PB2)
row4: D14.1 (K), D26.1 (K), D38.1 (K), D50.1 (K), D62.1 (K), D74.1 (K), D85.1 (K), U1.39 (PB3)
row5: D9.1 (K), D21.1 (K), D33.1 (K), D45.1 (K), D57.1 (K), D69.1 (K), D81.1 (K), D90.1 (K), U1.40 (PB4)
row6: D15.1 (K), D27.1 (K), D39.1 (K), D51.1 (K), D63.1 (K), D75.1 (K), D86.1 (K), U1.41 (PB5)
row7: D10.1 (K), D22.1 (K), D34.1 (K), D46.1 (K), D58.1 (K), D70.1 (K), D82.1 (K), U1.42 (PB6)
row8: D16.1 (K), D28.1 (K), D40.1 (K), D52.1 (K), D64.1 (K), D76.1 (K), D87.1 (K), U1.43 (PB7)
row9: D11.1 (K), D23.1 (K), D35.1 (K), D47.1 (K), D59.1 (K), D71.1 (K), D83.1 (K), U1.45 (PB8)
row10: D17.1 (K), D29.1 (K), D41.1 (K), D53.1 (K), D65.1 (K), D77.1 (K), D88.1 (K), U1.46 (PB9)
row11: D12.1 (K), D24.1 (K), D36.1 (K), D48.1 (K), D60.1 (K), D72.1 (K), U1.21 (PB10)
row12: D18.1 (K), D30.1 (K), D42.1 (K), D54.1 (K), D66.1 (K), D78.1 (K), U1.22 (PB11)

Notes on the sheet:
Keeb Power Supply
Keeb ARM Chip Decoupling Caps
Key Matrix
RGB Matrix Decoupling Capacitors
WS2812B RGB Backlight Matrix
Case ESD
USB ESD Protection
USB C IN
ARM CORTEX IC
Rotary Encoder
Serial Programmer
Keyboard
Indicator LED
Caps Lock LED

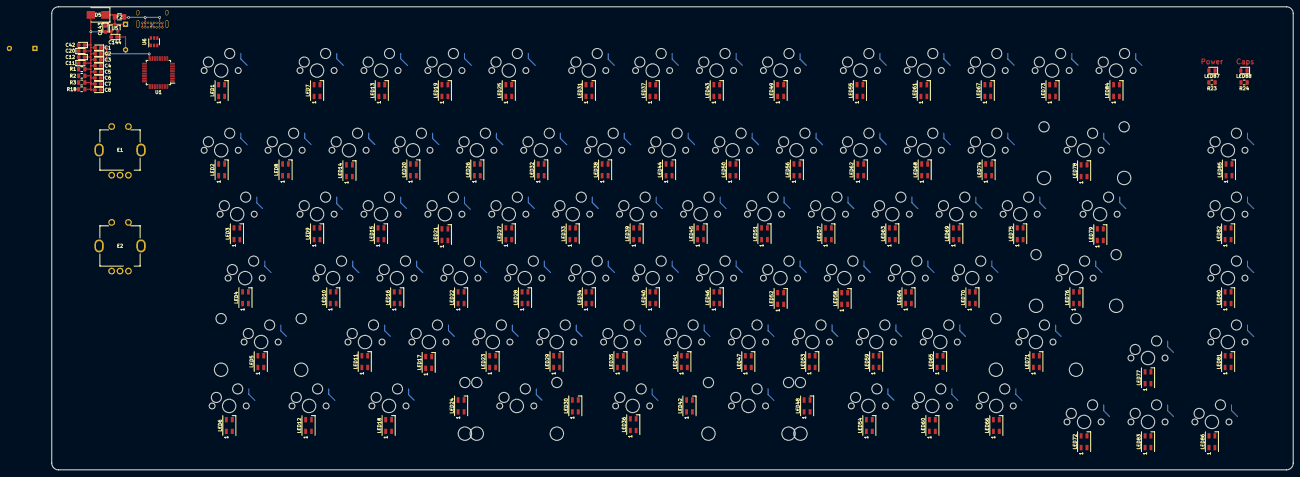
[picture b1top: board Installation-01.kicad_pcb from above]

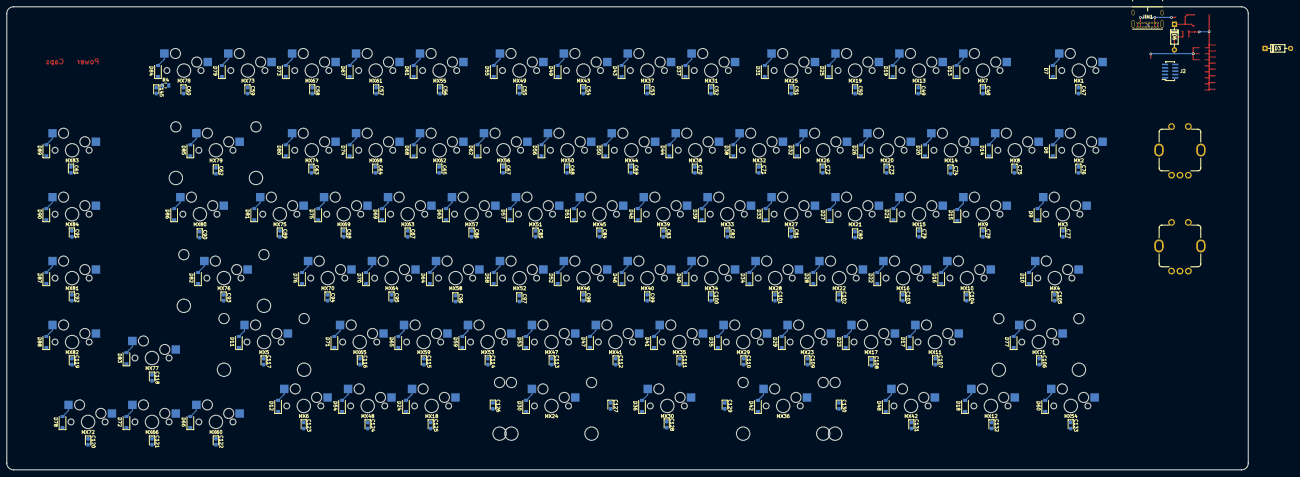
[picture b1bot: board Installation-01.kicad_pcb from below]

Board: 2 copper layers, 370.0 x 138.0 mm, 375 parts (176 on the bottom side), 216 nets.

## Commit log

2020-03-25 Add Submodules
2020-03-25 added libraries
2020-03-25 Added More Submodules
2020-03-25 Power and USB connectivity
2020-03-28 matrix and led library added
2020-03-28 per key lighting added
    -removed IS31FL3733 library as it existed in another library
    -using SK6812MINI individually addressable RGB LED's for per key lighting
2020-03-30 rgb fix and encoder library
2020-04-03 usb hub work
    +added usb power switches
    +added usb hub project and most of the schematic
2020-04-04 added usb hub back into keyboard
2020-04-12 Add hotswap sockets
2020-04-12 pcb start and hotswap boyz
2020-04-13 pcb start
2020-04-14 continued pcb
2020-04-16 pcb rgb finished
2020-04-17 pcb diode start
2020-04-19 pcb update
    +key matrix and pcb components placed
    +board outline
2020-04-21 more pcb
2020-04-22 Added Acheron Lib
2020-04-22 pcb changes
2020-04-29 Added Keyv2 Submodule
2020-04-29 reorganization of files and folders
2020-04-30 changed library path so stuff works
    hi i dont know how to use environmental variables in kicad until this commit :D
2020-04-30 Added KeyV2
2020-05-03 encoder
2020-05-03 3d model
2020-05-08 keyboard
2020-05-10 some bs with power management on pcb
2020-07-17 version change
    -added bleeding edge project
    -added version 1 project
2020-07-17 v1 board
2020-07-24 border
2020-09-15 removed mounting holes
2020-09-15 finished pcb
2020-09-16 added 3d models
    3d models for components and pcb
    plate svg n stuff
2020-09-16 more pcb 3d model updates
2020-09-16 logo stuff
2020-09-28 bruh moment
